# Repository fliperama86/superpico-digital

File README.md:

# SuperPico Digital

Digital-to-digital HDMI mod for 2-chip SNES consoles using the Raspberry Pi Pico 2 (RP2350B).

## Overview

SuperPico Digital captures native 15-bit digital RGB directly from the S-PPU2's TST pins - bypassing the console's analog video path entirely - and outputs clean HDMI via the RP2350's hardware HSTX peripheral. This approach eliminates the blur inherent in non - 1CHIP SNES consoles and provides a rock-solid, jitter-free image.

## Key Features

- **Hard Sync Architecture**: Uses physical `VBLANK` and `HBLANK` wires for perfect frame and line alignment.
- **Phase-Locked PIO Loop**: A custom PIO program synchronizes to the SNES Pixel Clock (`PCLK`) phase on every line, completely eliminating horizontal "hot air" jitter.
- **Jitter-Free 1:1 Capture**: Strategic setup delays ensure the raw SNES data bus is sampled at the peak of stability.
- **High Performance**: Leverages the RP2350 (Pico 2) HSTX peripheral for 640x480 @ 60Hz HDMI output.

## Hardware Requirements

- **Console**: 2-chip or 3-chip SNES (depending how you count :), e.g., SNS-CPU-GPM-01/02, SHVC-CPU-01.
- **NOT compatible with 1-CHIP consoles.**
- **Microcontroller**: Raspberry Pi Pico 2 (RP2350).
- **Video Signals**: Requires soldering to PPU2 pins for digital RGB, Sync, and Clock.

## Wiring Reference

### Capture Pins (GP27-GP44 contiguous, PIO1 with GPIOBASE=16)

| Signal     | SNES Source | Pico 2 GPIO | Capture Bit |
| ---------- | ----------- | ----------- | ----------- |
| **VBLANK** | PPU2 Pin 26 | GP27        | 0           |
| **PCLK**   | PPU2 Pin 27 | GP28        | 1           |
| **B4-B0**  | PPU2 TST    | GP29-33     | 2-6         |
| **G4-G0**  | PPU2 TST    | GP34-38     | 7-11        |
| **R4-R0**  | PPU2 TST    | GP39-43     | 12-16       |
| **HBLANK** | PPU2 Pin 25 | GP44        | 17          |

### HDMI Output

| Signal         | Pico 2 GPIO |
| -------------- | ----------- |
| **HDMI D0-D2** | GP14-19     |
| **HDMI CLK**   | GP12-13     |

## Build & Flash

### Prerequisites

- Pico SDK
- `arm-none-eabi-gcc` toolchain
- `picotool`

### Build Commands

```bash
# Configure
mkdir build && cd build
cmake .. -DPICO_SDK_PATH=/path/to/pico-sdk

# Compile
make -j8

# Flash
picotool load src/superpico-digital.uf2 -f && picotool reboot
```

## Current Status

- [x] Stable Hardware Sync (HBLANK/VBLANK)
- [x] Jitter-free Pixel Capture
- [x] HDMI Signal Stability (640x480)
- [x] Horizontal Centering and Offset Fixes
- [x] Full 15-bit RGB555 Color (32K LUT with per-channel bit-reversal → RGB565)
- [ ] Digital Audio capture
- [ ] Master Brightness Logic ($2100) - 6 GPIOs + 74HC4078
- [ ] Mode 7 Transparency (/OVER) — 1 GPIO, PPU1 pin 94
- [ ] Pixel Blanking (TOUMEI) — 1 GPIO, PPU2 pin 4

## Credits & References

- Based on logic from the **SNES_TST** FPGA project by Opatusos/michael-hirschmugl.
- Inspired by the **neopico-hd** project for MVS.
- Uses the **pico_hdmi** library for HSTX output.

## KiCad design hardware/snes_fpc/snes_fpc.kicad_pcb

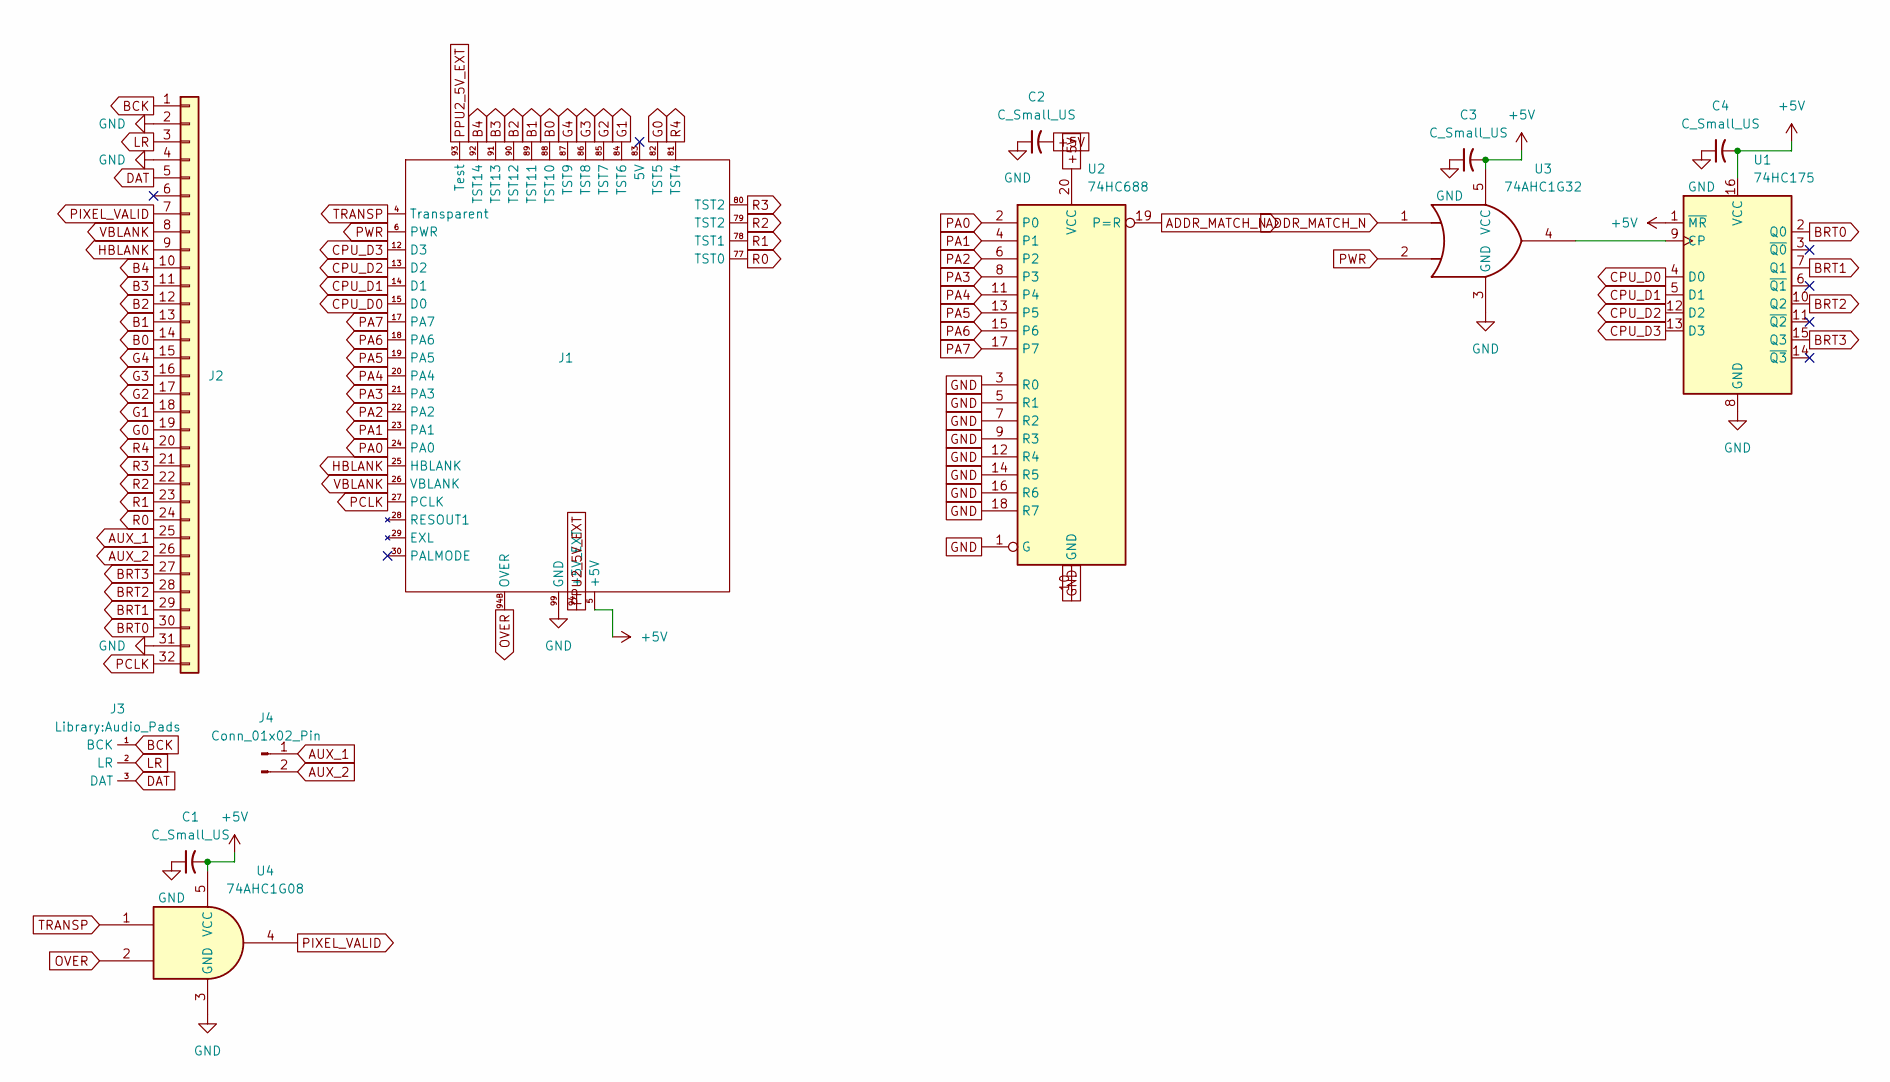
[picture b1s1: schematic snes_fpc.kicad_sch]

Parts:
C1, C2, C3, C4: C_Small_US; C_0402_1005Metric
J1: PPU2_FPC
J2: Connector_Generic:Conn_02x16_Counter_Clockwise; TE_3-1734839-2_1x32-1MP_P0.5mm_Horizontal
J3: Audio_Pads
J4: Conn_01x02_Pin; Controller_Pads
U1: 74HC175; TSSOP-16_4.4x5mm_P0.65mm; Manufacturer Part SN74HC175PWR; LCSC C2682067
U2: 74HC688; TSSOP-20_4.4x6.5mm_P0.65mm; Manufacturer Part SN74HC688PWR; LCSC C132045
U3: 74AHC1G32; SOT-23-5; Manufacturer Part SN74AHC1G32DBVR; LCSC C7470
U4: 74AHC1G08; SOT-23-5; Manufacturer Part SN74AHC1G08DBVR; LCSC C7467

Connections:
+5V: C1.2, C2.2, C3.2, C4.2, J1.5 (+5V), U1.1 (~MR), U1.16 (VCC), U2.20 (VCC), U3.5 (VCC), U4.5 (VCC)
ADDR_MATCH_N: U2.19 (P=R), U3.1
AUX_1: J2.25, J4.1
AUX_2: J2.26, J4.2
B0: J1.88 (TST10), J2.14
B1: J1.89 (TST11), J2.13
B2: J1.90 (TST12), J2.12
B3: J1.91 (TST13), J2.11
B4: J1.92 (TST14), J2.10
BCK: J2.1, J3.1 (BCK)
BRT0: J2.30, U1.2 (Q0)
BRT1: J2.29, U1.7 (Q1)
BRT2: J2.28, U1.10 (Q2)
BRT3: J2.27, U1.15 (Q3)
CPU_D0: J1.15 (D0), U1.4 (D0)
CPU_D1: J1.14 (D1), U1.5 (D1)
CPU_D2: J1.13 (D2), U1.12 (D2)
CPU_D3: J1.12 (D3), U1.13 (D3)
DAT: J2.5, J3.3 (DAT)
G0: J1.82 (TST5), J2.19
G1: J1.84 (TST6), J2.18
G2: J1.85 (TST7), J2.17
G3: J1.86 (TST8), J2.16
G4: J1.87 (TST9), J2.15
GND: C1.1, C2.1, C3.1, C4.1, J1.16 (GND), J1.99 (GND), J2.2, J2.4, J2.31, J2.MP, U1.8 (GND), U2.1 (G), U2.3 (R0), U2.5 (R1), U2.7 (R2), U2.9 (R3), U2.10 (GND), U2.12 (R4), U2.14 (R5), U2.16 (R6), U2.18 (R7), U3.3 (GND), U4.3 (GND)
HBLANK: J1.25 (HBLANK), J2.9
LR: J2.3, J3.2 (LR)
unnamed: U1.9 (CP), U3.4
OVER: J1.94B (OVER), U4.2
PA0: J1.24 (PA0), U2.2 (P0)
PA1: J1.23 (PA1), U2.4 (P1)
PA2: J1.22 (PA2), U2.6 (P2)
PA3: J1.21 (PA3), U2.8 (P3)
PA4: J1.20 (PA4), U2.11 (P4)
PA5: J1.19 (PA5), U2.13 (P5)
PA6: J1.18 (PA6), U2.15 (P6)
PA7: J1.17 (PA7), U2.17 (P7)
PCLK: J1.27 (PCLK), J2.32
PIXEL_VALID: J2.7, U4.4
PPU2_5V_EXT: J1.93 (Test), J1.94 (+5V_EXT)
PWR: J1.6 (PWR), U3.2
R0: J1.77 (TST0), J2.24
R1: J1.78 (TST1), J2.23
R2: J1.79 (TST2), J2.22
R3: J1.80 (TST2), J2.21
R4: J1.81 (TST4), J2.20
TRANSP: J1.4 (Transparent), U4.1
VBLANK: J1.26 (VBLANK), J2.8

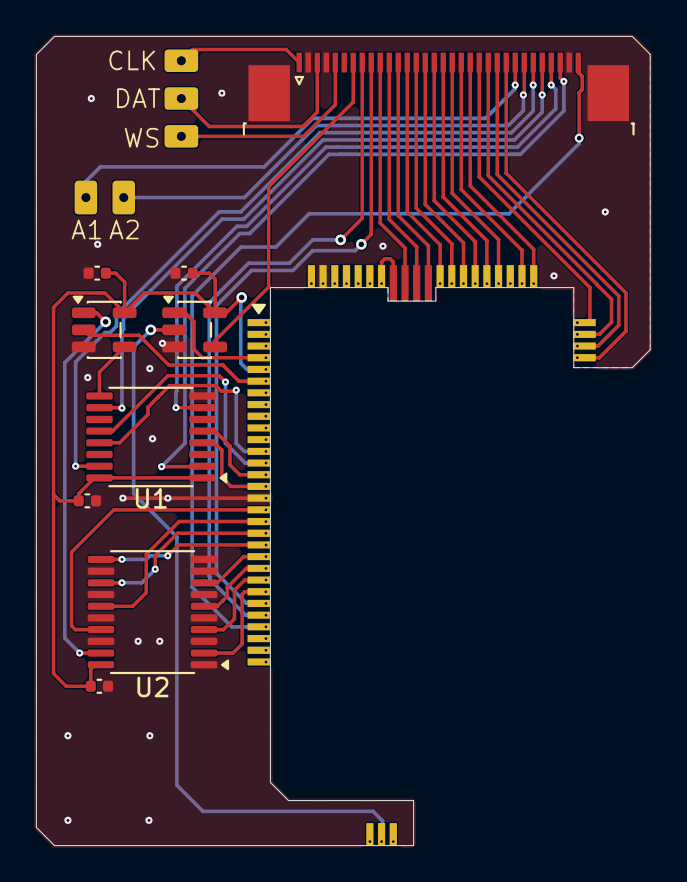
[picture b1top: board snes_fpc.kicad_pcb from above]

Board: 2 copper layers, 34.1 x 45.0 mm, 12 parts (0 on the bottom side), 48 nets.

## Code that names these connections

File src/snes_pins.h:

/**
 * SuperPico Digital - SNES Pin Configuration
 *
 * This file contains all SNES capture and sync pins.
 * Uses the same PCB layout as NeoPico-HD MVS; HBLANK/VBLANK occupy the
 * SHADOW/DARK positions. Contiguous 18-pin capture window: GP27-GP44.
 * CSYNC is not connected on this hardware.
 */

#ifndef SNES_PINS_H
#define SNES_PINS_H

// =============================================================================
// SNES Video Input Pins - GP27-44 CONTIGUOUS LAYOUT
// =============================================================================
// Captures RGB555 + VBLANK + HBLANK from the SNES PPU.
//
// 18-pin capture window: GP27 (LSB) through GP44 (MSB).
//
// Pin mapping (LSB to MSB in captured word):
//   Bit 0:      GP27 (VBLANK) - PPU2 Pin 26
//   Bit 1:      GP28 (PCLK)   - PPU2 Pin 27
//   Bits 2-6:   GP29-33 (Blue B4-B0, contiguous)
//   Bits 7-11:  GP34-38 (Green G4-G0, contiguous)
//   Bits 12-16: GP39-43 (Red R4-R0, contiguous)
//   Bit 17:     GP44 (HBLANK) - PPU2 Pin 25
//
// With PIO GPIOBASE=16, pin index N = GP(N+16). So IN_BASE=11 → GP27.

// Sync / blanking
#define PIN_SNES_VBLANK 27 // Vertical blanking   - Bit 0  (PPU2 Pin 26)
#define PIN_SNES_PCLK   28 // Pixel clock (~5.37 MHz, Bit 1, PPU2 Pin 27)
#define PIN_SNES_BASE   27 // Base pin - capture GP27-44 (18 pins)

// Blue channel (B4-B0) - CONTIGUOUS at bits 2-6
#define PIN_SNES_B4 29
#define PIN_SNES_B3 30
#define PIN_SNES_B2 31
#define PIN_SNES_B1 32
#define PIN_SNES_B0 33

// Green channel (G4-G0) - CONTIGUOUS at bits 7-11
#define PIN_SNES_G4 34
#define PIN_SNES_G3 35
#define PIN_SNES_G2 36
#define PIN_SNES_G1 37
#define PIN_SNES_G0 38

// Red channel (R4-R0) - CONTIGUOUS at bits 12-16
#define PIN_SNES_R4 39
#define PIN_SNES_R3 40
#define PIN_SNES_R2 41
#define PIN_SNES_R1 42
#define PIN_SNES_R0 43

// Blanking
#define PIN_SNES_HBLANK 44 // Horizontal blanking - Bit 17 (PPU2 Pin 25)

#define SNES_CAPTURE_PIN_LAST PIN_SNES_HBLANK
#define SNES_CAPTURE_BITS     18

// =============================================================================
// Frequency Counter Pin Aliases (for debug tools)
// =============================================================================
#define PIN_FREQ_PCLK   PIN_SNES_PCLK
#define PIN_FREQ_R0     PIN_SNES_R0
#define PIN_FREQ_VBLANK PIN_SNES_VBLANK

// =============================================================================
// Audio I2S Pins - GP22-24 (SNES S-DSP)
// =============================================================================
#define PIN_AUDIO_SDATA 22  // GP22 - S-DSP Pin 44 (serial data)
#define PIN_AUDIO_LRCK  23  // GP23 - S-DSP Pin 43 (word select / L-R clock)
#define PIN_AUDIO_BCLK  24  // GP24 - S-DSP Pin 42 (bit clock)

// =============================================================================
// S-DSP Control Signals - GP6-7
// =============================================================================
#define PIN_AUDIO_DCK    6  // GP6  - S-DSP Pin 78 (master clock, 8.192 MHz)
#define PIN_AUDIO_RESET  7  // GP7  - S-DSP Pin 47 (/RESET, active-low)

// =============================================================================
// OSD Buttons - GP25-26
// =============================================================================
#define PIN_OSD_BTN_MENU 25 // Active-low menu/select button
#define PIN_OSD_BTN_BACK 26 // Active-low back/cycle button

#endif // SNES_PINS_H

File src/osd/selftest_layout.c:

#include "selftest_layout.h"

#include "fast_osd.h"

#define ST_TITLE_ROW 1
#define ST_TITLE_COL 2
#define ST_SPINNER_COL 25

#define ST_VIDEO_ROW 3
#define ST_VIDEO_LABEL_ROW 4
#define ST_BITS_HEADER_ROW 6
#define ST_RED_ROW 7
#define ST_GREEN_ROW 8
#define ST_BLUE_ROW 9

#define ST_VBLANK_COL 1
#define ST_VBLANK_ICON_COL 6
#define ST_PCLK_COL 9
#define ST_PCLK_ICON_COL 13
#define ST_HBLANK_COL 16
#define ST_HBLANK_ICON_COL 21

#define ST_AUDIO_ROW 11
#define ST_AUDIO_LABEL_ROW 12
#define ST_DCK_ROW 14

static inline void selftest_render_icon(uint8_t row, uint8_t col, bool ok)
{
    fast_osd_putc_color(row, col, ok ? FAST_OSD_GLYPH_CHECK : '-', ok ? OSD_COLOR_GREEN : OSD_COLOR_GRAY);
}

static inline void selftest_render_icon_neutral(uint8_t row, uint8_t col)
{
    fast_osd_putc_color(row, col, '-', OSD_COLOR_GRAY);
}

void selftest_layout_reset(void)
{
    fast_osd_clear();

    fast_osd_puts_color(ST_TITLE_ROW, ST_TITLE_COL, "SuperPico Self Test", OSD_COLOR_YELLOW);

    fast_osd_puts(ST_VIDEO_ROW, 1, "Video");
    fast_osd_puts_color(ST_VIDEO_LABEL_ROW, ST_VBLANK_COL, "VBLK", OSD_COLOR_GRAY);
    fast_osd_puts_color(ST_VIDEO_LABEL_ROW, ST_PCLK_COL, "PCLK", OSD_COLOR_GRAY);
    fast_osd_puts_color(ST_VIDEO_LABEL_ROW, ST_HBLANK_COL, "HBLK", OSD_COLOR_GRAY);

    fast_osd_puts_color(ST_BITS_HEADER_ROW, 8, "0", OSD_COLOR_GRAY);
    fast_osd_puts_color(ST_BITS_HEADER_ROW, 10, "1", OSD_COLOR_GRAY);
    fast_osd_puts_color(ST_BITS_HEADER_ROW, 12, "2", OSD_COLOR_GRAY);
    fast_osd_puts_color(ST_BITS_HEADER_ROW, 14, "3", OSD_COLOR_GRAY);
    fast_osd_puts_color(ST_BITS_HEADER_ROW, 16, "4", OSD_COLOR_GRAY);

    fast_osd_puts_color(ST_RED_ROW, 1, "Red", OSD_COLOR_GRAY);
    fast_osd_puts_color(ST_GREEN_ROW, 1, "Green", OSD_COLOR_GRAY);
    fast_osd_puts_color(ST_BLUE_ROW, 1, "Blue", OSD_COLOR_GRAY);

    fast_osd_puts(ST_AUDIO_ROW, 1, "Audio");
    fast_osd_puts_color(ST_AUDIO_LABEL_ROW, 1, "BCK", OSD_COLOR_GRAY);
    fast_osd_puts_color(ST_AUDIO_LABEL_ROW, 10, "WS", OSD_COLOR_GRAY);
    fast_osd_puts_color(ST_AUDIO_LABEL_ROW, 18, "DAT", OSD_COLOR_GRAY);
    fast_osd_puts_color(ST_DCK_ROW, 1, "DCK", OSD_COLOR_GRAY);

    selftest_render_icon_neutral(ST_VIDEO_LABEL_ROW, ST_VBLANK_ICON_COL);
    selftest_render_icon_neutral(ST_VIDEO_LABEL_ROW, ST_PCLK_ICON_COL);
    selftest_render_icon_neutral(ST_VIDEO_LABEL_ROW, ST_HBLANK_ICON_COL);

    for (uint8_t col = 8; col <= 16; col += 2) {
        selftest_render_icon_neutral(ST_RED_ROW, col);
        selftest_render_icon_neutral(ST_GREEN_ROW, col);
        selftest_render_icon_neutral(ST_BLUE_ROW, col);
    }

    selftest_render_icon_neutral(ST_AUDIO_LABEL_ROW, 5);
    selftest_render_icon_neutral(ST_AUDIO_LABEL_ROW, 14);
    selftest_render_icon_neutral(ST_AUDIO_LABEL_ROW, 22);
    selftest_render_icon_neutral(ST_DCK_ROW, 5);
}

void selftest_layout_update(uint32_t frame_count, bool has_snapshot, uint32_t toggled_bits)
{
    static uint8_t dat_hold = 0;
    static const uint32_t red_bits[5] = {SELFTEST_BIT_R0, SELFTEST_BIT_R1, SELFTEST_BIT_R2, SELFTEST_BIT_R3,
                                         SELFTEST_BIT_R4};
    static const uint32_t green_bits[5] = {SELFTEST_BIT_G0, SELFTEST_BIT_G1, SELFTEST_BIT_G2, SELFTEST_BIT_G3,
                                           SELFTEST_BIT_G4};
    static const uint32_t blue_bits[5] = {SELFTEST_BIT_B0, SELFTEST_BIT_B1, SELFTEST_BIT_B2, SELFTEST_BIT_B3,
                                          SELFTEST_BIT_B4};
    static const char spinner[4] = {'|', '/', '-', '\\'};
    const char spin = spinner[(frame_count / 60U) & 3U];
    fast_osd_putc_color(ST_TITLE_ROW, ST_SPINNER_COL, spin, OSD_COLOR_YELLOW);

    if (!has_snapshot) {
        return;
    }

    selftest_render_icon(ST_VIDEO_LABEL_ROW, ST_VBLANK_ICON_COL, (toggled_bits & SELFTEST_BIT_VBLANK) != 0U);
    selftest_render_icon(ST_VIDEO_LABEL_ROW, ST_PCLK_ICON_COL, (toggled_bits & SELFTEST_BIT_PCLK) != 0U);
    selftest_render_icon(ST_VIDEO_LABEL_ROW, ST_HBLANK_ICON_COL, (toggled_bits & SELFTEST_BIT_HBLANK) != 0U);

    for (uint8_t i = 0; i < 5; i++) {
        const uint8_t col = (uint8_t)(8U + (i * 2U));
        selftest_render_icon(ST_RED_ROW, col, (toggled_bits & red_bits[i]) != 0U);
        selftest_render_icon(ST_GREEN_ROW, col, (toggled_bits & green_bits[i]) != 0U);
        selftest_render_icon(ST_BLUE_ROW, col, (toggled_bits & blue_bits[i]) != 0U);
    }

    selftest_render_icon(ST_AUDIO_LABEL_ROW, 5, (toggled_bits & SELFTEST_BIT_BCK) != 0U);
    selftest_render_icon(ST_AUDIO_LABEL_ROW, 14, (toggled_bits & SELFTEST_BIT_WS) != 0U);
    selftest_render_icon(ST_DCK_ROW, 5, (toggled_bits & SELFTEST_BIT_DCK) != 0U);

    if ((toggled_bits & SELFTEST_BIT_DAT) != 0U) {
        dat_hold = 5;
    } else if (dat_hold > 0U) {
        dat_hold--;
    }
    selftest_render_icon(ST_AUDIO_LABEL_ROW, 22, dat_hold > 0U);
}

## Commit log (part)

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2026-01-18 Integrate PicoHDMI
2026-01-18 Freq counter
2026-01-18 Ignore obsidian files
2026-01-18 grid + osd + line2x
2026-01-18 First capture
2026-01-19 Some image
2026-01-19 Fix hot air distortion
2026-01-19 Fix frame width. Update docs
2026-01-19 Update docs
2026-01-19 Enable audio
2026-01-19 Test audio
2026-01-20 Remove old flag
2026-02-28 Adjust to work with neopico-hd PCB
2026-02-28 Update docs. Full color cap working!
2026-02-28 Improve cap reliability
2026-02-28 Add Digital Audio capture to feature list
2026-02-28 Improve sync
2026-03-20 Correct Raspberry Pi Pico model in README
    Updated the model number of the Raspberry Pi Pico in the README.
2026-06-27 Add audio bringup notes and hardware references
2026-06-27 Update scratchbook after publish
